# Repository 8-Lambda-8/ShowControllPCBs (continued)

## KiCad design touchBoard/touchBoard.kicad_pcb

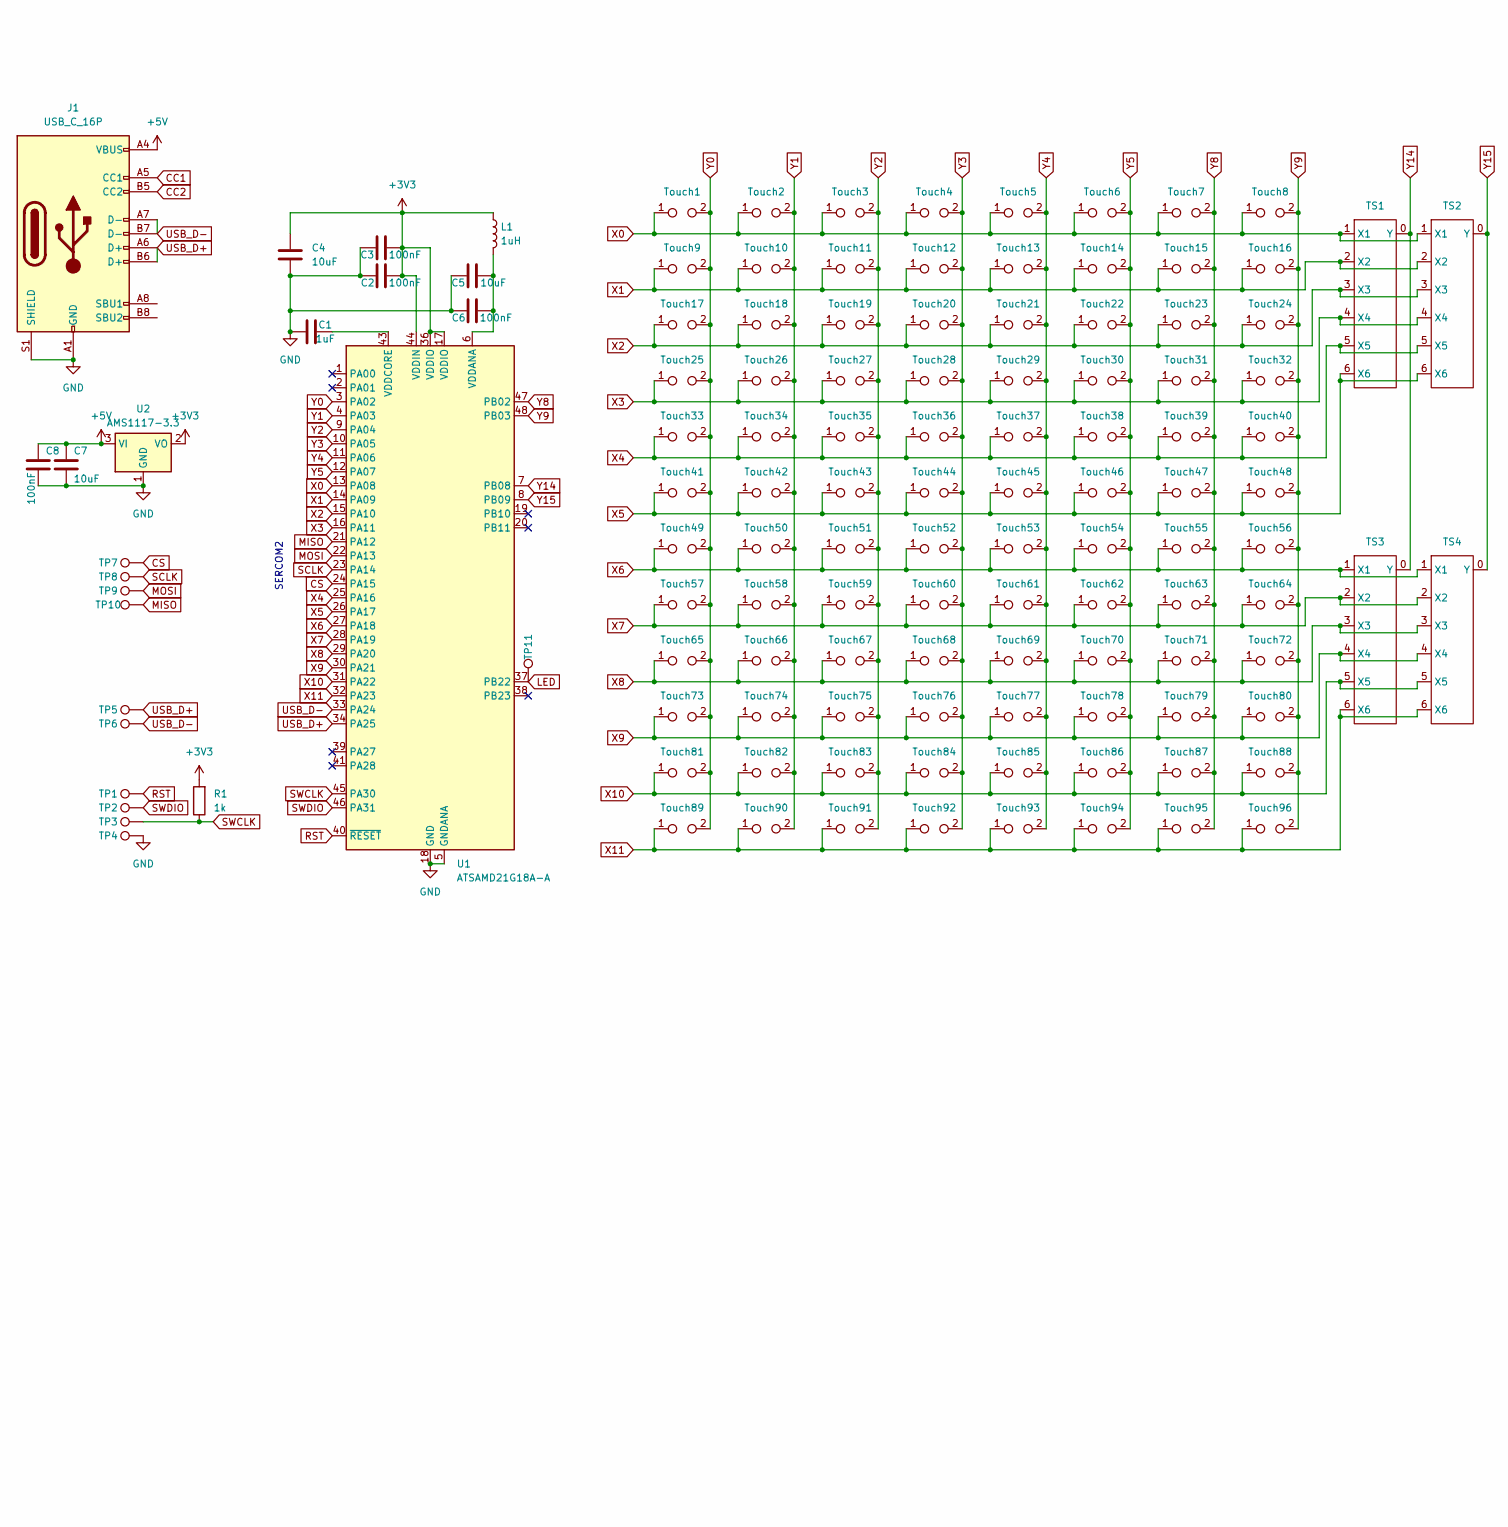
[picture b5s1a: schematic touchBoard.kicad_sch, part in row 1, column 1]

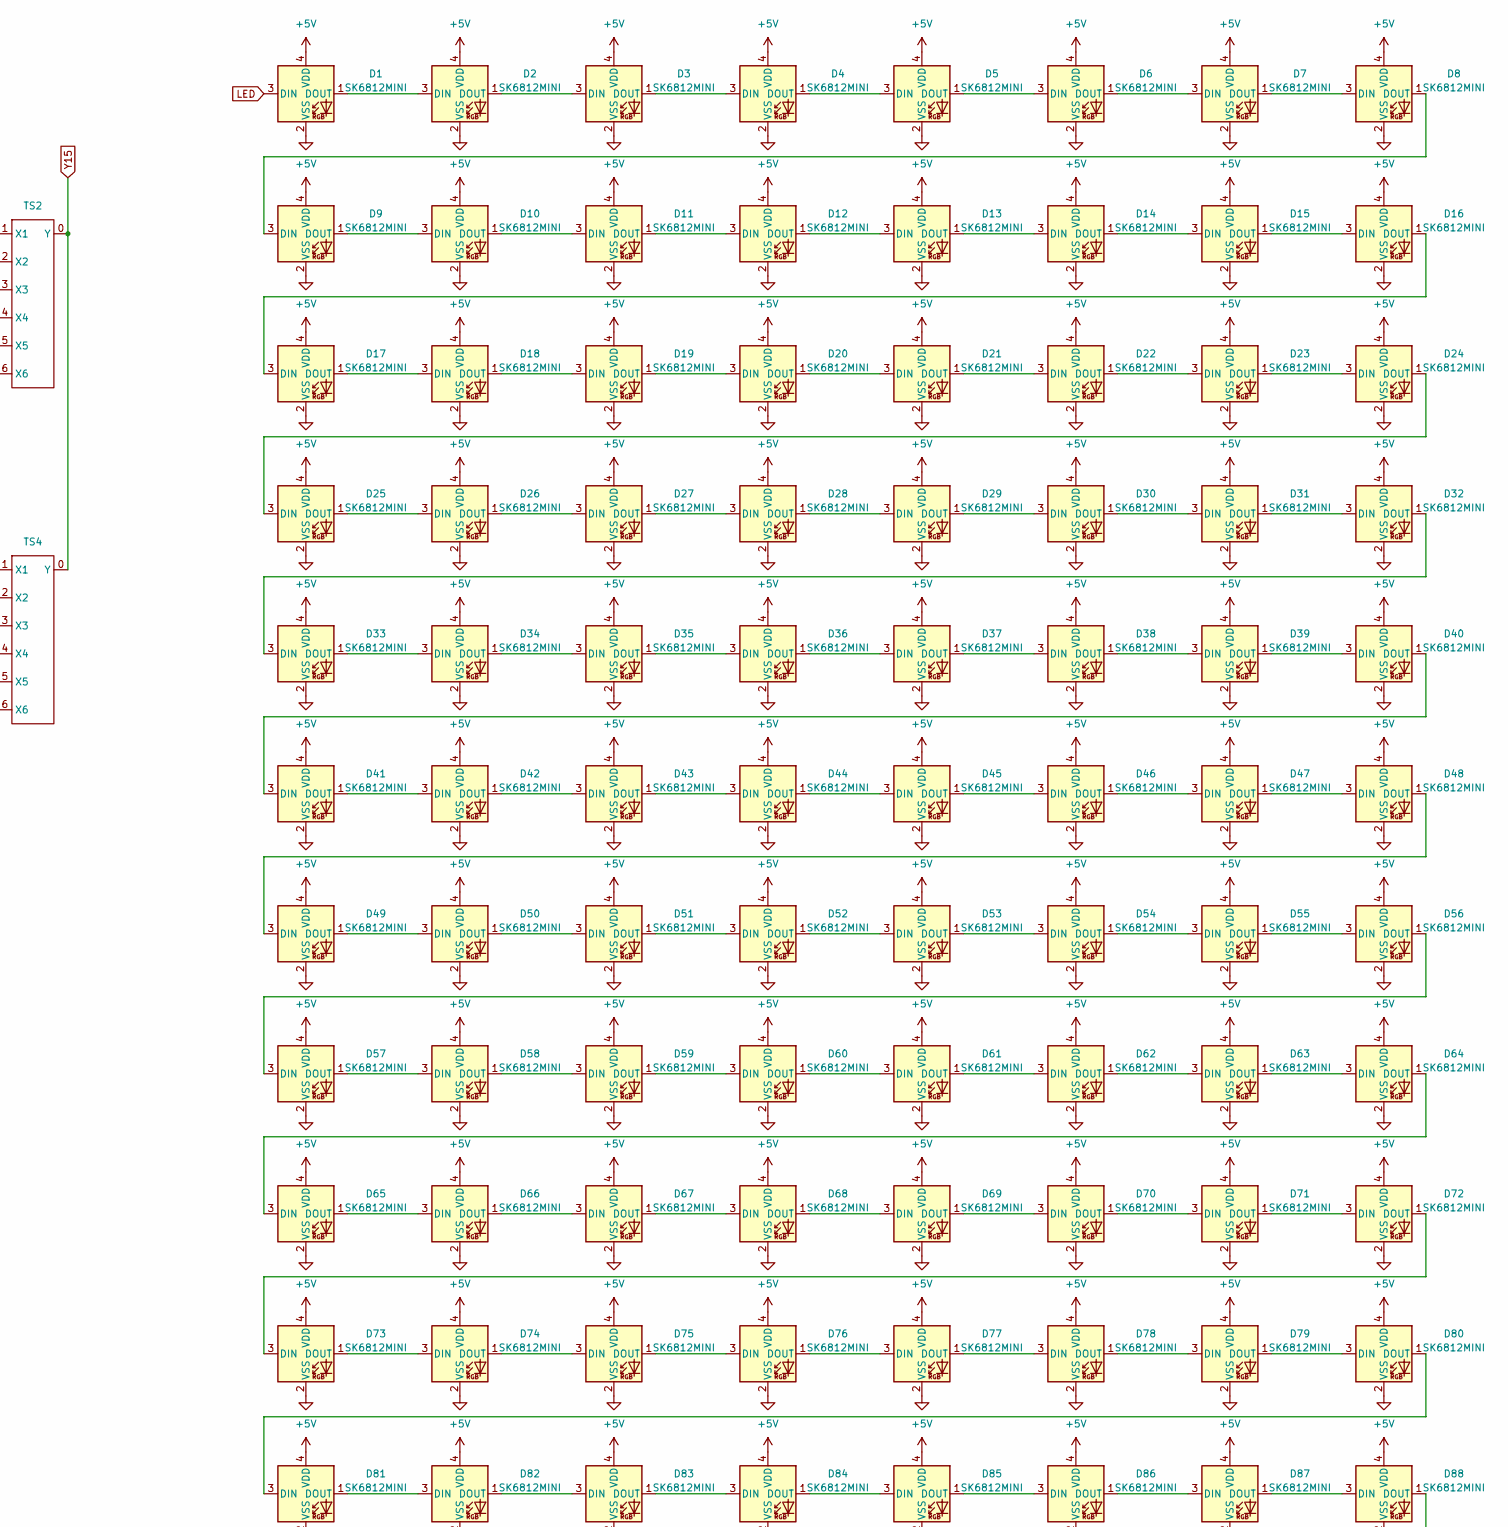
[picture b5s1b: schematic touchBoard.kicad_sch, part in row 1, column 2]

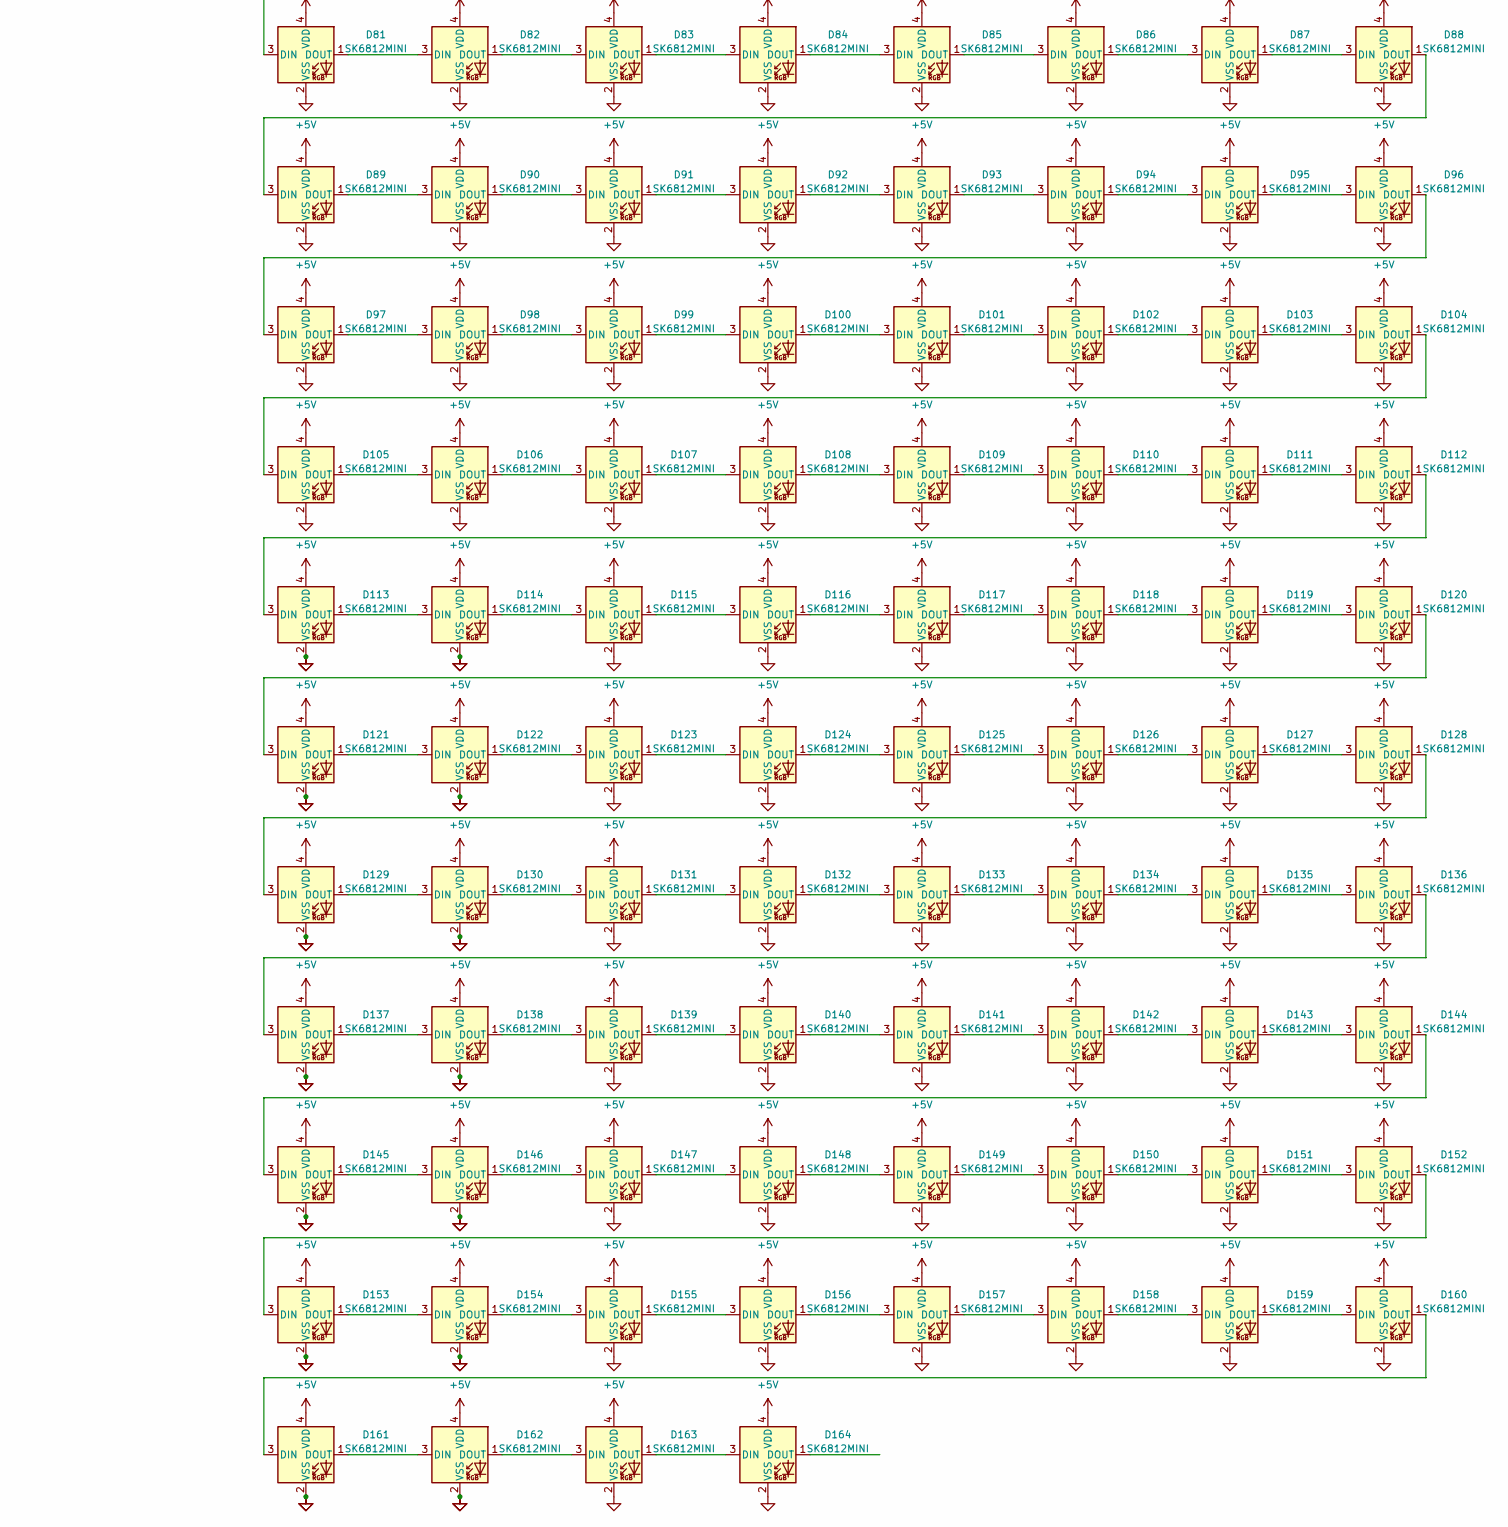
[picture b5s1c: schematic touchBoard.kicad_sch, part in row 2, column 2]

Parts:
C1: 1uF; C_0805_2012Metric_Pad1.18x1.45mm_HandSolder
C2, C3, C6, C8: 100nF; C_0805_2012Metric_Pad1.18x1.45mm_HandSolder
C4, C5, C7: 10uF; C_0805_2012Metric_Pad1.18x1.45mm_HandSolder
D1, D2, D3, D4, D5, D6, D7, D8, D9, D10, D11, D12, D13, D14, D15, D16, D17, D18, D19, D20, D21, D22, D23, D24, D25, D26, D27, D28, D29, D30, D31, D32, D33, D34, D35, D36, D37, D38, D39, D40, D41, D42, D43, D44, D45, D46, D47, D48, D49, D50, D51, D52, D53, D54, D55, D56, D57, D58, D59, D60, D61, D62, D63, D64, D65, D66, D67, D68, D69, D70, D71, D72, D73, D74, D75, D76, D77, D78, D79, D80, D81, D82, D83, D84, D85, D86, D87, D88, D89, D90, D91, D92, D93, D94, D95, D96, D97, D98, D99, D100, D101, D102, D103, D104, D105, D106, D107, D108, D109, D110, D111, D112, D113, D114, D115, D116, D117, D118, D119, D120, D121, D122, D123, D124, D125, D126, D127, D128, D129, D130, D131, D132, D133, D134, D135, D136, D137, D138, D139, D140, D141, D142, D143, D144, D145, D146, D147, D148, D149, D150, D151, D152, D153, D154, D155, D156, D157, D158, D159, D160, D161, D162, D163, D164: SK6812MINI; LED_SK6812MINI_PLCC4_3.5x3.5mm_P1.75mm
J1: USB_C_16P; USB_C_Receptacle_HCTL_HC-TYPE-C-16P-01A
L1: 1uH; L_0805_2012Metric_Pad1.15x1.40mm_HandSolder
R1: 1k; R_0805_2012Metric_Pad1.20x1.40mm_HandSolder
TP1: RST; TestPoint_Pad_D1.5mm
TP2: SWDIO; TestPoint_Pad_D1.5mm
TP3: SWCLK; TestPoint_Pad_D1.5mm
TP4: GND; TestPoint_Pad_D1.5mm
TP5: USB_D+; TestPoint_Pad_D1.5mm
TP6: USB_D-; TestPoint_Pad_D1.5mm
TP7: CS; TestPoint_Pad_D1.5mm
TP8: SCLK; TestPoint_Pad_D1.5mm
TP9: MOSI; TestPoint_Pad_D1.5mm
TP10: MISO; TestPoint_Pad_D1.5mm
TP11: LED; TestPoint_Pad_D1.5mm
TS1, TS2, TS3, TS4: TouchSlider
Touch1, Touch2, Touch3, Touch4, Touch5, Touch6, Touch7, Touch8, Touch9, Touch10, Touch11, Touch12, Touch13, Touch14, Touch15, Touch16, Touch17, Touch18, Touch19, Touch20, Touch21, Touch22, Touch23, Touch24, Touch25, Touch26, Touch27, Touch28, Touch29, Touch30, Touch31, Touch32, Touch33, Touch34, Touch35, Touch36, Touch37, Touch38, Touch39, Touch40, Touch41, Touch42, Touch43, Touch44, Touch45, Touch46, Touch47, Touch48, Touch49, Touch50, Touch51, Touch52, Touch53, Touch54, Touch55, Touch56, Touch57, Touch58, Touch59, Touch60, Touch61, Touch62, Touch63, Touch64, Touch65, Touch66, Touch67, Touch68, Touch69, Touch70, Touch71, Touch72, Touch73, Touch74, Touch75, Touch76, Touch77, Touch78, Touch79, Touch80, Touch81, Touch82, Touch83, Touch84, Touch85, Touch86, Touch87, Touch88, Touch89, Touch90, Touch91, Touch92, Touch93, Touch94, Touch95, Touch96: TestPoint_2Pole; TouchButton
U1: ATSAMD21G18A-A; TQFP-48_7x7mm_P0.5mm
U2: AMS1117-3.3; SOT-223-3_TabPin2

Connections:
+3V3: C2.2, C3.1, C4.1, L1.1, R1.2, U1.17 (VDDIO), U1.36 (VDDIO), U1.44 (VDDIN), U2.2 (VO)
+5V: C7.1, C8.1, D1.4 (VDD), D2.4 (VDD), D3.4 (VDD), D4.4 (VDD), D5.4 (VDD), D6.4 (VDD), D7.4 (VDD), D8.4 (VDD), D9.4 (VDD), D10.4 (VDD), D11.4 (VDD), D12.4 (VDD), D13.4 (VDD), D14.4 (VDD), D15.4 (VDD), D16.4 (VDD), D17.4 (VDD), D18.4 (VDD), D19.4 (VDD), D20.4 (VDD), D21.4 (VDD), D22.4 (VDD), D23.4 (VDD), D24.4 (VDD), D25.4 (VDD), D26.4 (VDD), D27.4 (VDD), D28.4 (VDD), D29.4 (VDD), D30.4 (VDD), D31.4 (VDD), D32.4 (VDD), D33.4 (VDD), D34.4 (VDD), D35.4 (VDD), D36.4 (VDD), D37.4 (VDD), D38.4 (VDD), D39.4 (VDD), D40.4 (VDD), D41.4 (VDD), D42.4 (VDD), D43.4 (VDD), D44.4 (VDD), D45.4 (VDD), D46.4 (VDD), D47.4 (VDD), D48.4 (VDD), D49.4 (VDD), D50.4 (VDD), D51.4 (VDD), D52.4 (VDD), D53.4 (VDD), D54.4 (VDD), D55.4 (VDD), D56.4 (VDD), D57.4 (VDD), D58.4 (VDD), D59.4 (VDD), D60.4 (VDD), D61.4 (VDD), D62.4 (VDD), D63.4 (VDD), D64.4 (VDD), D65.4 (VDD), D66.4 (VDD), D67.4 (VDD), D68.4 (VDD), D69.4 (VDD), D70.4 (VDD), D71.4 (VDD), D72.4 (VDD), D73.4 (VDD), D74.4 (VDD), D75.4 (VDD), D76.4 (VDD), D77.4 (VDD), D78.4 (VDD), D79.4 (VDD), D80.4 (VDD), D81.4 (VDD), D82.4 (VDD), D83.4 (VDD), D84.4 (VDD), D85.4 (VDD), D86.4 (VDD), D87.4 (VDD), D88.4 (VDD), D89.4 (VDD), D90.4 (VDD), D91.4 (VDD), D92.4 (VDD), D93.4 (VDD), D94.4 (VDD), D95.4 (VDD), D96.4 (VDD), D97.4 (VDD), D98.4 (VDD), D99.4 (VDD), D100.4 (VDD), D101.4 (VDD), D102.4 (VDD), D103.4 (VDD), D104.4 (VDD), D105.4 (VDD), D106.4 (VDD), D107.4 (VDD), D108.4 (VDD), D109.4 (VDD), D110.4 (VDD), D111.4 (VDD), D112.4 (VDD), D113.4 (VDD), D114.4 (VDD), D115.4 (VDD), D116.4 (VDD), D117.4 (VDD), D118.4 (VDD), D119.4 (VDD), D120.4 (VDD), D121.4 (VDD), D122.4 (VDD), D123.4 (VDD), D124.4 (VDD), D125.4 (VDD), D126.4 (VDD), D127.4 (VDD), D128.4 (VDD), D129.4 (VDD), D130.4 (VDD), D131.4 (VDD), D132.4 (VDD), D133.4 (VDD), D134.4 (VDD), D135.4 (VDD), D136.4 (VDD), D137.4 (VDD), D138.4 (VDD), D139.4 (VDD), D140.4 (VDD), D141.4 (VDD), D142.4 (VDD), D143.4 (VDD), D144.4 (VDD), D145.4 (VDD), D146.4 (VDD), D147.4 (VDD), D148.4 (VDD), D149.4 (VDD), D150.4 (VDD), D151.4 (VDD), D152.4 (VDD), D153.4 (VDD), D154.4 (VDD), D155.4 (VDD), D156.4 (VDD), D157.4 (VDD), D158.4 (VDD), D159.4 (VDD), D160.4 (VDD), D161.4 (VDD), D162.4 (VDD), D163.4 (VDD), D164.4 (VDD), J1.A4 (VBUS), J1.A9 (VBUS), J1.B4 (VBUS), J1.B9 (VBUS), U2.3 (VI)
CC1: J1.A5 (CC1)
CC2: J1.B5 (CC2)
CS: TP7.1, U1.24 (PA15)
GND: C1.2, C2.1, C3.2, C4.2, C5.2, C6.1, C7.2, C8.2, D1.2 (VSS), D2.2 (VSS), D3.2 (VSS), D4.2 (VSS), D5.2 (VSS), D6.2 (VSS), D7.2 (VSS), D8.2 (VSS), D9.2 (VSS), D10.2 (VSS), D11.2 (VSS), D12.2 (VSS), D13.2 (VSS), D14.2 (VSS), D15.2 (VSS), D16.2 (VSS), D17.2 (VSS), D18.2 (VSS), D19.2 (VSS), D20.2 (VSS), D21.2 (VSS), D22.2 (VSS), D23.2 (VSS), D24.2 (VSS), D25.2 (VSS), D26.2 (VSS), D27.2 (VSS), D28.2 (VSS), D29.2 (VSS), D30.2 (VSS), D31.2 (VSS), D32.2 (VSS), D33.2 (VSS), D34.2 (VSS), D35.2 (VSS), D36.2 (VSS), D37.2 (VSS), D38.2 (VSS), D39.2 (VSS), D40.2 (VSS), D41.2 (VSS), D42.2 (VSS), D43.2 (VSS), D44.2 (VSS), D45.2 (VSS), D46.2 (VSS), D47.2 (VSS), D48.2 (VSS), D49.2 (VSS), D50.2 (VSS), D51.2 (VSS), D52.2 (VSS), D53.2 (VSS), D54.2 (VSS), D55.2 (VSS), D56.2 (VSS), D57.2 (VSS), D58.2 (VSS), D59.2 (VSS), D60.2 (VSS), D61.2 (VSS), D62.2 (VSS), D63.2 (VSS), D64.2 (VSS), D65.2 (VSS), D66.2 (VSS), D67.2 (VSS), D68.2 (VSS), D69.2 (VSS), D70.2 (VSS), D71.2 (VSS), D72.2 (VSS), D73.2 (VSS), D74.2 (VSS), D75.2 (VSS), D76.2 (VSS), D77.2 (VSS), D78.2 (VSS), D79.2 (VSS), D80.2 (VSS), D81.2 (VSS), D82.2 (VSS), D83.2 (VSS), D84.2 (VSS), D85.2 (VSS), D86.2 (VSS), D87.2 (VSS), D88.2 (VSS), D89.2 (VSS), D90.2 (VSS), D91.2 (VSS), D92.2 (VSS), D93.2 (VSS), D94.2 (VSS), D95.2 (VSS), D96.2 (VSS), D97.2 (VSS), D98.2 (VSS), D99.2 (VSS), D100.2 (VSS), D101.2 (VSS), D102.2 (VSS), D103.2 (VSS), D104.2 (VSS), D105.2 (VSS), D106.2 (VSS), D107.2 (VSS), D108.2 (VSS), D109.2 (VSS), D110.2 (VSS), D111.2 (VSS), D112.2 (VSS), D113.2 (VSS), D114.2 (VSS), D115.2 (VSS), D116.2 (VSS), D117.2 (VSS), D118.2 (VSS), D119.2 (VSS), D120.2 (VSS), D121.2 (VSS), D122.2 (VSS), D123.2 (VSS), D124.2 (VSS), D125.2 (VSS), D126.2 (VSS), D127.2 (VSS), D128.2 (VSS), D129.2 (VSS), D130.2 (VSS), D131.2 (VSS), D132.2 (VSS), D133.2 (VSS), D134.2 (VSS), D135.2 (VSS), D136.2 (VSS), D137.2 (VSS), D138.2 (VSS), D139.2 (VSS), D140.2 (VSS), D141.2 (VSS), D142.2 (VSS), D143.2 (VSS), D144.2 (VSS), D145.2 (VSS), D146.2 (VSS), D147.2 (VSS), D148.2 (VSS), D149.2 (VSS), D150.2 (VSS), D151.2 (VSS), D152.2 (VSS), D153.2 (VSS), D154.2 (VSS), D155.2 (VSS), D156.2 (VSS), D157.2 (VSS), D158.2 (VSS), D159.2 (VSS), D160.2 (VSS), D161.2 (VSS), D162.2 (VSS), D163.2 (VSS), D164.2 (VSS), J1.A1 (GND), J1.A12 (GND), J1.B1 (GND), J1.B12 (GND), J1.S1 (SHIELD), TP4.1, U1.5 (GNDANA), U1.18 (GND), U1.35 (GND), U1.42 (GND), U2.1 (GND)
LED: D1.3 (DIN), TP11.1, U1.37 (PB22)
MISO: TP10.1, U1.21 (PA12)
MOSI: TP9.1, U1.22 (PA13)
unnamed: D1.1 (DOUT), D2.3 (DIN)
unnamed: D2.1 (DOUT), D3.3 (DIN)
unnamed: D3.1 (DOUT), D4.3 (DIN)
unnamed: D4.1 (DOUT), D5.3 (DIN)
unnamed: D5.1 (DOUT), D6.3 (DIN)
unnamed: D6.1 (DOUT), D7.3 (DIN)
unnamed: D7.1 (DOUT), D8.3 (DIN)
unnamed: D8.1 (DOUT), D9.3 (DIN)
unnamed: D9.1 (DOUT), D10.3 (DIN)
unnamed: D10.1 (DOUT), D11.3 (DIN)
unnamed: D11.1 (DOUT), D12.3 (DIN)
unnamed: D12.1 (DOUT), D13.3 (DIN)
unnamed: D13.1 (DOUT), D14.3 (DIN)
unnamed: D14.1 (DOUT), D15.3 (DIN)
unnamed: D15.1 (DOUT), D16.3 (DIN)
unnamed: D16.1 (DOUT), D17.3 (DIN)
unnamed: D17.1 (DOUT), D18.3 (DIN)
unnamed: D18.1 (DOUT), D19.3 (DIN)
unnamed: D19.1 (DOUT), D20.3 (DIN)
unnamed: D20.1 (DOUT), D21.3 (DIN)
unnamed: D21.1 (DOUT), D22.3 (DIN)
unnamed: D22.1 (DOUT), D23.3 (DIN)
unnamed: D23.1 (DOUT), D24.3 (DIN)
unnamed: D24.1 (DOUT), D25.3 (DIN)
unnamed: D25.1 (DOUT), D26.3 (DIN)
unnamed: D26.1 (DOUT), D27.3 (DIN)
unnamed: D27.1 (DOUT), D28.3 (DIN)
unnamed: D28.1 (DOUT), D29.3 (DIN)
unnamed: D29.1 (DOUT), D30.3 (DIN)
unnamed: D30.1 (DOUT), D31.3 (DIN)
unnamed: D31.1 (DOUT), D32.3 (DIN)
unnamed: D32.1 (DOUT), D33.3 (DIN)
unnamed: D33.1 (DOUT), D34.3 (DIN)
unnamed: D34.1 (DOUT), D35.3 (DIN)
unnamed: D35.1 (DOUT), D36.3 (DIN)
unnamed: D36.1 (DOUT), D37.3 (DIN)
unnamed: D37.1 (DOUT), D38.3 (DIN)
unnamed: D38.1 (DOUT), D39.3 (DIN)
unnamed: D39.1 (DOUT), D40.3 (DIN)
unnamed: D40.1 (DOUT), D41.3 (DIN)
unnamed: D41.1 (DOUT), D42.3 (DIN)
unnamed: D42.1 (DOUT), D43.3 (DIN)
unnamed: D43.1 (DOUT), D44.3 (DIN)
unnamed: D44.1 (DOUT), D45.3 (DIN)
unnamed: D45.1 (DOUT), D46.3 (DIN)
unnamed: D46.1 (DOUT), D47.3 (DIN)
unnamed: D47.1 (DOUT), D48.3 (DIN)
unnamed: D48.1 (DOUT), D49.3 (DIN)
unnamed: D49.1 (DOUT), D50.3 (DIN)
unnamed: D50.1 (DOUT), D51.3 (DIN)
unnamed: D51.1 (DOUT), D52.3 (DIN)
unnamed: D52.1 (DOUT), D53.3 (DIN)
unnamed: D53.1 (DOUT), D54.3 (DIN)
unnamed: D54.1 (DOUT), D55.3 (DIN)
unnamed: D55.1 (DOUT), D56.3 (DIN)
unnamed: D56.1 (DOUT), D57.3 (DIN)
unnamed: D57.1 (DOUT), D58.3 (DIN)
unnamed: D58.1 (DOUT), D59.3 (DIN)
unnamed: D59.1 (DOUT), D60.3 (DIN)
unnamed: D60.1 (DOUT), D61.3 (DIN)
unnamed: D61.1 (DOUT), D62.3 (DIN)
unnamed: D62.1 (DOUT), D63.3 (DIN)
unnamed: D63.1 (DOUT), D64.3 (DIN)
unnamed: D64.1 (DOUT), D65.3 (DIN)
unnamed: D65.1 (DOUT), D66.3 (DIN)
unnamed: D66.1 (DOUT), D67.3 (DIN)
unnamed: D67.1 (DOUT), D68.3 (DIN)
unnamed: D68.1 (DOUT), D69.3 (DIN)
unnamed: D69.1 (DOUT), D70.3 (DIN)
unnamed: D70.1 (DOUT), D71.3 (DIN)
unnamed: D71.1 (DOUT), D72.3 (DIN)
unnamed: D72.1 (DOUT), D73.3 (DIN)
unnamed: D73.1 (DOUT), D74.3 (DIN)
unnamed: D74.1 (DOUT), D75.3 (DIN)
unnamed: D75.1 (DOUT), D76.3 (DIN)
unnamed: D76.1 (DOUT), D77.3 (DIN)
unnamed: D77.1 (DOUT), D78.3 (DIN)
unnamed: D78.1 (DOUT), D79.3 (DIN)
unnamed: D79.1 (DOUT), D80.3 (DIN)
unnamed: D80.1 (DOUT), D81.3 (DIN)
unnamed: D81.1 (DOUT), D82.3 (DIN)
unnamed: D82.1 (DOUT), D83.3 (DIN)
unnamed: D83.1 (DOUT), D84.3 (DIN)
unnamed: D84.1 (DOUT), D85.3 (DIN)
unnamed: D85.1 (DOUT), D86.3 (DIN)
unnamed: D86.1 (DOUT), D87.3 (DIN)
unnamed: D87.1 (DOUT), D88.3 (DIN)
unnamed: D88.1 (DOUT), D89.3 (DIN)
unnamed: D89.1 (DOUT), D90.3 (DIN)
unnamed: D90.1 (DOUT), D91.3 (DIN)
unnamed: D91.1 (DOUT), D92.3 (DIN)
unnamed: D92.1 (DOUT), D93.3 (DIN)
unnamed: D93.1 (DOUT), D94.3 (DIN)
unnamed: D94.1 (DOUT), D95.3 (DIN)
unnamed: D95.1 (DOUT), D96.3 (DIN)
unnamed: D96.1 (DOUT), D97.3 (DIN)
unnamed: D97.1 (DOUT), D98.3 (DIN)
unnamed: D98.1 (DOUT), D99.3 (DIN)
unnamed: D99.1 (DOUT), D100.3 (DIN)
unnamed: D100.1 (DOUT), D101.3 (DIN)
unnamed: D101.1 (DOUT), D102.3 (DIN)
unnamed: D102.1 (DOUT), D103.3 (DIN)
unnamed: D103.1 (DOUT), D104.3 (DIN)
unnamed: D104.1 (DOUT), D105.3 (DIN)
unnamed: D105.1 (DOUT), D106.3 (DIN)
unnamed: D106.1 (DOUT), D107.3 (DIN)
unnamed: D107.1 (DOUT), D108.3 (DIN)
unnamed: D108.1 (DOUT), D109.3 (DIN)
unnamed: D109.1 (DOUT), D110.3 (DIN)
unnamed: D110.1 (DOUT), D111.3 (DIN)
unnamed: D111.1 (DOUT), D112.3 (DIN)
unnamed: D112.1 (DOUT), D113.3 (DIN)
unnamed: D113.1 (DOUT), D114.3 (DIN)
unnamed: D114.1 (DOUT), D115.3 (DIN)
unnamed: D115.1 (DOUT), D116.3 (DIN)
unnamed: D116.1 (DOUT), D117.3 (DIN)
unnamed: D117.1 (DOUT), D118.3 (DIN)
unnamed: D118.1 (DOUT), D119.3 (DIN)
unnamed: D119.1 (DOUT), D120.3 (DIN)
unnamed: D120.1 (DOUT), D121.3 (DIN)
unnamed: D121.1 (DOUT), D122.3 (DIN)
unnamed: D122.1 (DOUT), D123.3 (DIN)
unnamed: D123.1 (DOUT), D124.3 (DIN)
unnamed: D124.1 (DOUT), D125.3 (DIN)
unnamed: D125.1 (DOUT), D126.3 (DIN)
unnamed: D126.1 (DOUT), D127.3 (DIN)
unnamed: D127.1 (DOUT), D128.3 (DIN)
unnamed: D128.1 (DOUT), D129.3 (DIN)
unnamed: D129.1 (DOUT), D130.3 (DIN)
unnamed: D130.1 (DOUT), D131.3 (DIN)
unnamed: D131.1 (DOUT), D132.3 (DIN)
unnamed: D132.1 (DOUT), D133.3 (DIN)
unnamed: D133.1 (DOUT), D134.3 (DIN)
unnamed: D134.1 (DOUT), D135.3 (DIN)
unnamed: D135.1 (DOUT), D136.3 (DIN)
unnamed: D136.1 (DOUT), D137.3 (DIN)
unnamed: D137.1 (DOUT), D138.3 (DIN)
unnamed: D138.1 (DOUT), D139.3 (DIN)
unnamed: D139.1 (DOUT), D140.3 (DIN)
unnamed: D140.1 (DOUT), D141.3 (DIN)
unnamed: D141.1 (DOUT), D142.3 (DIN)
unnamed: D142.1 (DOUT), D143.3 (DIN)
unnamed: D143.1 (DOUT), D144.3 (DIN)
unnamed: D144.1 (DOUT), D145.3 (DIN)
unnamed: D145.1 (DOUT), D146.3 (DIN)
unnamed: D146.1 (DOUT), D147.3 (DIN)
unnamed: D147.1 (DOUT), D148.3 (DIN)
unnamed: D148.1 (DOUT), D149.3 (DIN)
unnamed: D149.1 (DOUT), D150.3 (DIN)
unnamed: D150.1 (DOUT), D151.3 (DIN)
unnamed: D151.1 (DOUT), D152.3 (DIN)
unnamed: D152.1 (DOUT), D153.3 (DIN)
unnamed: D153.1 (DOUT), D154.3 (DIN)
unnamed: D154.1 (DOUT), D155.3 (DIN)
unnamed: D155.1 (DOUT), D156.3 (DIN)
unnamed: D156.1 (DOUT), D157.3 (DIN)
unnamed: D157.1 (DOUT), D158.3 (DIN)
unnamed: D158.1 (DOUT), D159.3 (DIN)
unnamed: D159.1 (DOUT), D160.3 (DIN)
unnamed: D160.1 (DOUT), D161.3 (DIN)
unnamed: D161.1 (DOUT), D162.3 (DIN)
unnamed: D162.1 (DOUT), D163.3 (DIN)
unnamed: D163.1 (DOUT), D164.3 (DIN)
unnamed: C5.1, C6.2, L1.2, U1.6 (VDDANA)
unnamed: C1.1, U1.43 (VDDCORE)
RST: TP1.1, U1.40 (~RESET)
SCLK: TP8.1, U1.23 (PA14)
SWCLK: R1.1, TP3.1, U1.45 (PA30)
SWDIO: TP2.1, U1.46 (PA31)
USB_D+: J1.A6 (D+), J1.B6 (D+), TP5.1, U1.34 (PA25)
USB_D-: J1.A7 (D-), J1.B7 (D-), TP6.1, U1.33 (PA24)
X0: TS1.1 (X1), TS2.1 (X1), Touch1.1, Touch2.1, Touch3.1, Touch4.1, Touch5.1, Touch6.1, Touch7.1, Touch8.1, U1.13 (PA08)
X1: TS1.2 (X2), TS2.2 (X2), Touch9.1, Touch10.1, Touch11.1, Touch12.1, Touch13.1, Touch14.1, Touch15.1, Touch16.1, U1.14 (PA09)
X2: TS1.3 (X3), TS2.3 (X3), Touch17.1, Touch18.1, Touch19.1, Touch20.1, Touch21.1, Touch22.1, Touch23.1, Touch24.1, U1.15 (PA10)
X3: TS1.4 (X4), TS2.4 (X4), Touch25.1, Touch26.1, Touch27.1, Touch28.1, Touch29.1, Touch30.1, Touch31.1, Touch32.1, U1.16 (PA11)
X4: TS1.5 (X5), TS2.5 (X5), Touch33.1, Touch34.1, Touch35.1, Touch36.1, Touch37.1, Touch38.1, Touch39.1, Touch40.1, U1.25 (PA16)
X5: TS1.6 (X6), TS2.6 (X6), Touch41.1, Touch42.1, Touch43.1, Touch44.1, Touch45.1, Touch46.1, Touch47.1, Touch48.1, U1.26 (PA17)
X6: TS3.1 (X1), TS4.1 (X1), Touch49.1, Touch50.1, Touch51.1, Touch52.1, Touch53.1, Touch54.1, Touch55.1, Touch56.1, U1.27 (PA18)
X7: TS3.2 (X2), TS4.2 (X2), Touch57.1, Touch58.1, Touch59.1, Touch60.1, Touch61.1, Touch62.1, Touch63.1, Touch64.1, U1.28 (PA19)
X8: TS3.3 (X3), TS4.3 (X3), Touch65.1, Touch66.1, Touch67.1, Touch68.1, Touch69.1, Touch70.1, Touch71.1, Touch72.1, U1.29 (PA20)
X9: TS3.4 (X4), TS4.4 (X4), Touch73.1, Touch74.1, Touch75.1, Touch76.1, Touch77.1, Touch78.1, Touch79.1, Touch80.1, U1.30 (PA21)
X10: TS3.5 (X5), TS4.5 (X5), Touch81.1, Touch82.1, Touch83.1, Touch84.1, Touch85.1, Touch86.1, Touch87.1, Touch88.1, U1.31 (PA22)
X11: TS3.6 (X6), TS4.6 (X6), Touch89.1, Touch90.1, Touch91.1, Touch92.1, Touch93.1, Touch94.1, Touch95.1, Touch96.1, U1.32 (PA23)
Y0: Touch1.2, Touch9.2, Touch17.2, Touch25.2, Touch33.2, Touch41.2, Touch49.2, Touch57.2, Touch65.2, Touch73.2, Touch81.2, Touch89.2, U1.3 (PA02)
Y1: Touch2.2, Touch10.2, Touch18.2, Touch26.2, Touch34.2, Touch42.2, Touch50.2, Touch58.2, Touch66.2, Touch74.2, Touch82.2, Touch90.2, U1.4 (PA03)
Y2: Touch3.2, Touch11.2, Touch19.2, Touch27.2, Touch35.2, Touch43.2, Touch51.2, Touch59.2, Touch67.2, Touch75.2, Touch83.2, Touch91.2, U1.9 (PA04)
Y3: Touch4.2, Touch12.2, Touch20.2, Touch28.2, Touch36.2, Touch44.2, Touch52.2, Touch60.2, Touch68.2, Touch76.2, Touch84.2, Touch92.2, U1.10 (PA05)
Y4: Touch5.2, Touch13.2, Touch21.2, Touch29.2, Touch37.2, Touch45.2, Touch53.2, Touch61.2, Touch69.2, Touch77.2, Touch85.2, Touch93.2, U1.11 (PA06)
Y5: Touch6.2, Touch14.2, Touch22.2, Touch30.2, Touch38.2, Touch46.2, Touch54.2, Touch62.2, Touch70.2, Touch78.2, Touch86.2, Touch94.2, U1.12 (PA07)
Y8: Touch7.2, Touch15.2, Touch23.2, Touch31.2, Touch39.2, Touch47.2, Touch55.2, Touch63.2, Touch71.2, Touch79.2, Touch87.2, Touch95.2, U1.47 (PB02)
Y9: Touch8.2, Touch16.2, Touch24.2, Touch32.2, Touch40.2, Touch48.2, Touch56.2, Touch64.2, Touch72.2, Touch80.2, Touch88.2, Touch96.2, U1.48 (PB03)
Y14: TS1.0 (Y), TS3.0 (Y), U1.7 (PB08)
Y15: TS2.0 (Y), TS4.0 (Y), U1.8 (PB09)

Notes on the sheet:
SERCOM2

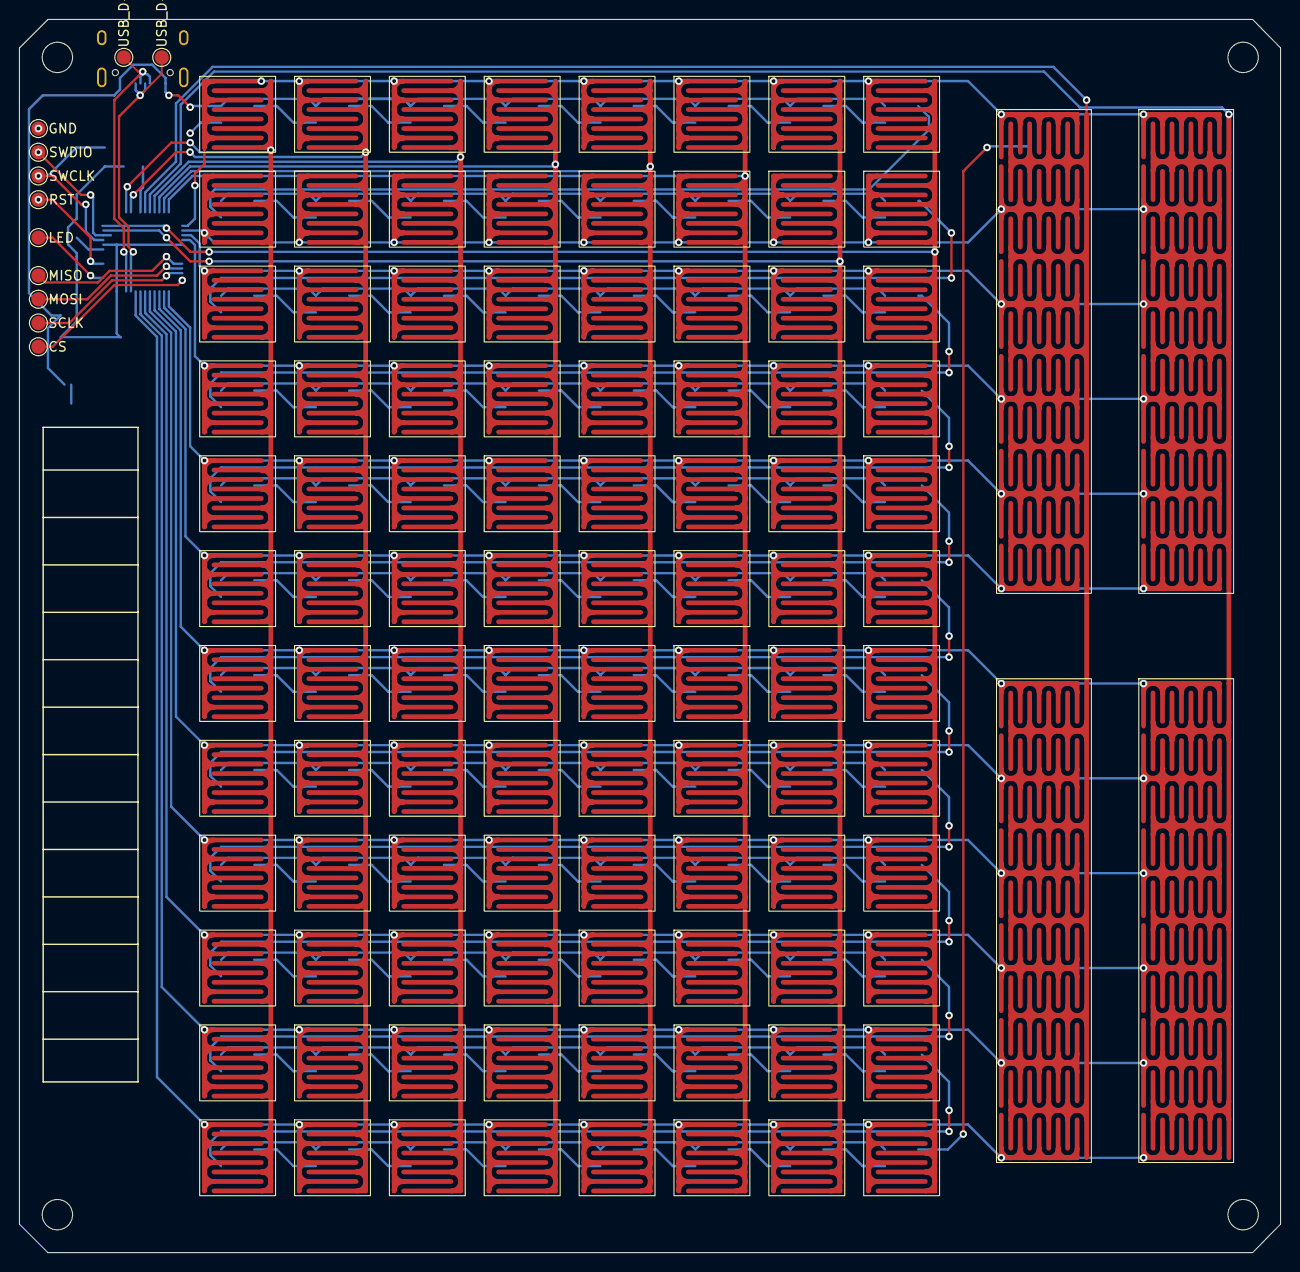
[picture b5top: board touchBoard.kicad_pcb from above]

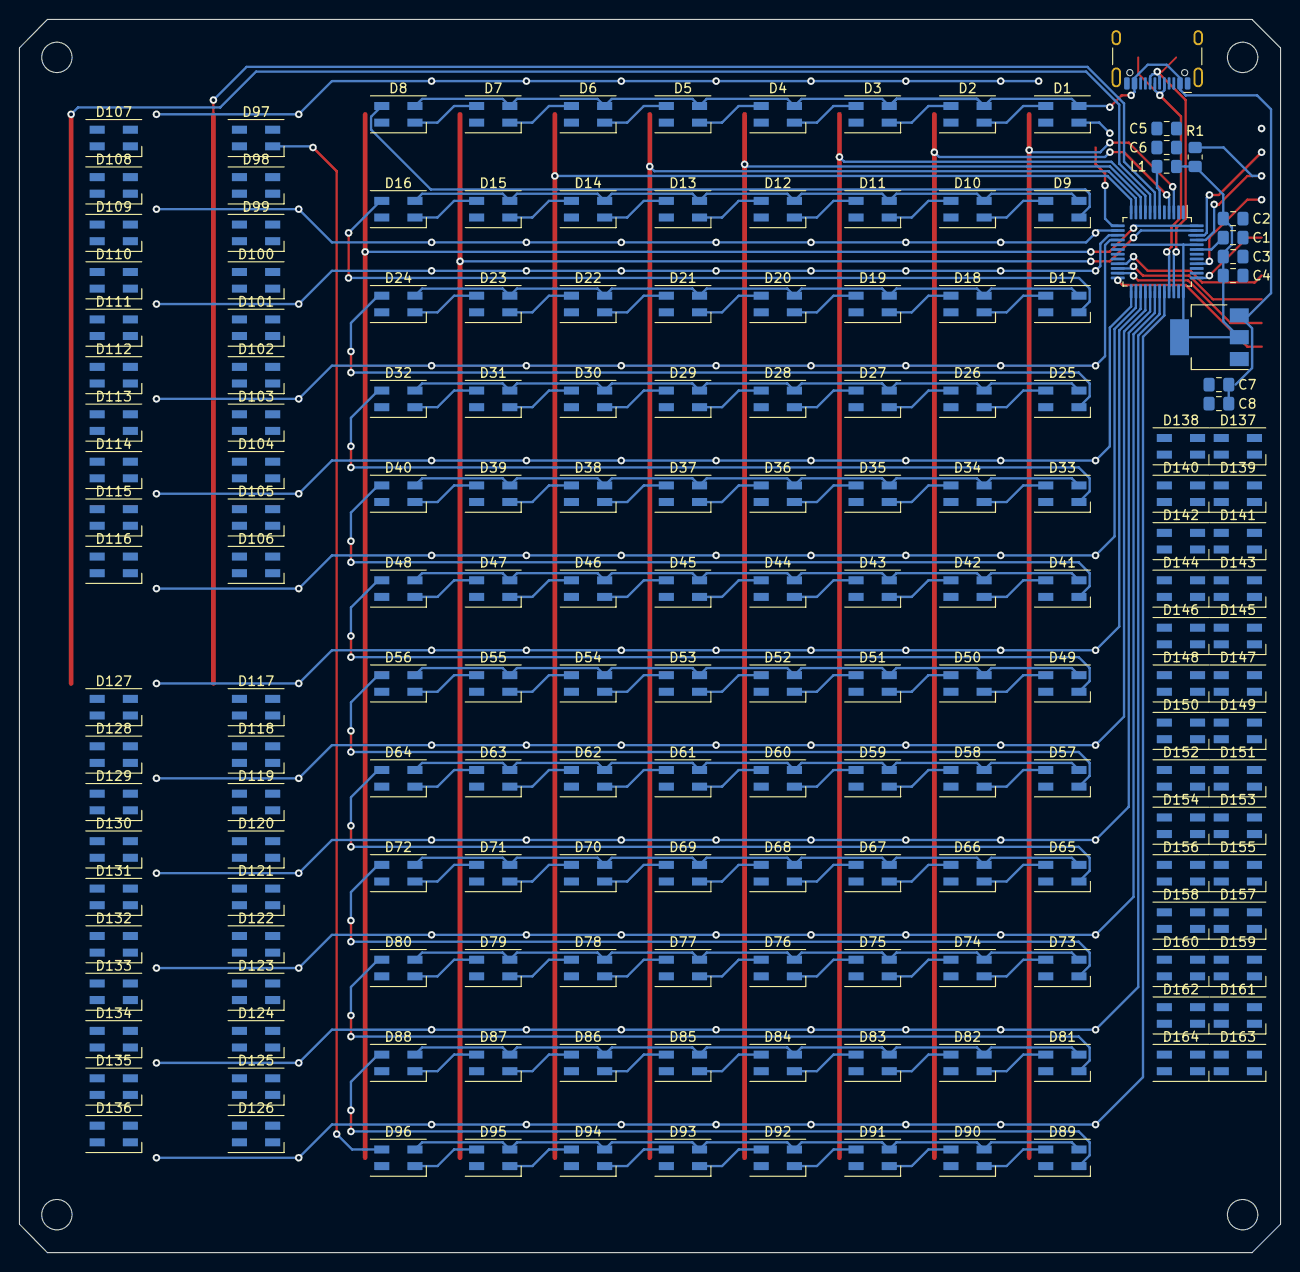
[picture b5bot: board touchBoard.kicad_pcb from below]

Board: 2 copper layers, 132.9 x 130.0 mm, 288 parts (177 on the bottom side), 200 nets.

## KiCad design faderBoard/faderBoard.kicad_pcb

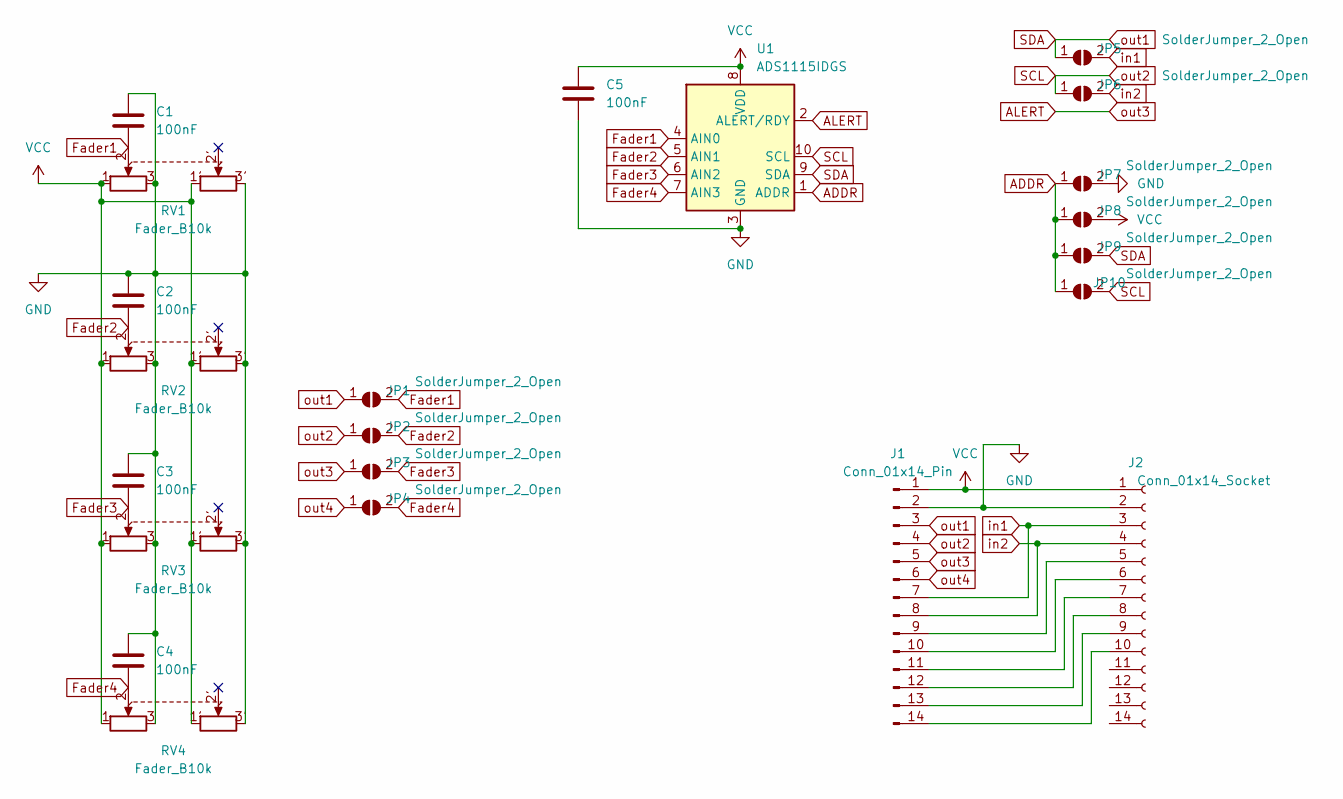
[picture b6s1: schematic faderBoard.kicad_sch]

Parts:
C1, C2, C3, C4, C5: 100nF; C_0805_2012Metric_Pad1.18x1.45mm_HandSolder
J1: Conn_01x14_Pin; PinHeader_1x14_P2.54mm_Vertical
J2: Conn_01x14_Socket; PinSocket_1x14_P2.54mm_Vertical
JP1, JP2, JP3, JP4, JP5, JP6, JP7, JP8, JP9, JP10: SolderJumper_2_Open; SolderJumper-2_P1.3mm_Open_RoundedPad1.0x1.5mm
RV1, RV2, RV3, RV4: Fader_B10k; Fader B10K
U1: ADS1115IDGS; TSSOP-10_3x3mm_P0.5mm

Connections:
ADDR: JP7.1 (A), JP8.1 (A), JP9.1 (A), JP10.1 (A), U1.1 (ADDR)
ALERT: J1.5, JP3.1 (A), U1.2 (ALERT/RDY); also elsewhere on the board
Fader1: C1.2, JP1.2 (B), RV1.2, U1.4 (AIN0)
Fader2: C2.2, JP2.2 (B), RV2.2, U1.5 (AIN1)
Fader3: C3.2, JP3.2 (B), RV3.2, U1.6 (AIN2)
Fader4: C4.2, JP4.2 (B), RV4.2, U1.7 (AIN3)
GND: C1.1, C2.1, C3.1, C4.1, C5.2, J1.2, J2.2, JP7.2 (B), RV1.3, RV1.3', RV2.3, RV2.3', RV3.3, RV3.3', RV4.3, RV4.3', U1.3 (GND); also elsewhere on the board
unnamed 7: J1.9, J2.5; also elsewhere on the board
unnamed 8: J1.10, J2.6; also elsewhere on the board
unnamed 9: J1.11, J2.7; also elsewhere on the board
unnamed 10: J1.12, J2.8; also elsewhere on the board
unnamed 11: J1.13, J2.9; also elsewhere on the board
unnamed 12: J1.14, J2.10; also elsewhere on the board
SCL: J1.4, JP2.1 (A), JP6.1 (A), JP10.2 (B), U1.10 (SCL); also elsewhere on the board
SDA: J1.3, JP1.1 (A), JP5.1 (A), JP9.2 (B), U1.9 (SDA); also elsewhere on the board
VCC: C5.1, J1.1, J2.1, JP8.2 (B), RV1.1, RV1.1', RV2.1, RV2.1', RV3.1, RV3.1', RV4.1, RV4.1', U1.8 (VDD); also elsewhere on the board
in1: J1.7, J2.3, JP5.2 (B); also elsewhere on the board
in2: J1.8, J2.4, JP6.2 (B); also elsewhere on the board
out4: J1.6, JP4.1 (A); also elsewhere on the board
